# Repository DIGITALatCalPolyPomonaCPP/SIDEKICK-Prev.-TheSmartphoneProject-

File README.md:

# SIDEKICK — The Smartphone Project

**SIDEKICK, previously named TheSmartphoneProject, is DIGITAL @ Cal Poly Pomona's flagship systems-engineering project: a student-designed modular smartphone built around an FPGA-based computing platform.** It treats the phone as one integrated product spanning programmable logic, circuit design, embedded software, operating systems, sensing, user interaction, mechanical design, and thermal engineering.

<p align="center">
  
</p>

<p align="center"><em>FPGA smartphone mainboard prototype. <a href="https://photos.app.goo.gl/fKSVxjnxUvrLaF7E6">View the project photo album.</a></em></p>

**Repository status:** This is an archival engineering snapshot. It consolidates original design files, subsystem iterations, planning documents, curricula, and project updates that were previously distributed across multiple repositories and contributor archives. It does not claim that every subsystem reached production readiness or that the files currently assemble into a finished phone.

## Executive summary

Technology has always evolved. What has changed is the pace at which innovation reshapes the world around us. Entire industries can now emerge, mature, and reinvent themselves within the span of a student's undergraduate education. Artificial intelligence is reshaping knowledge-based work, robotics is moving from laboratories into homes and industry, and manufacturing is becoming increasingly autonomous.

**The technologies that will define our students' careers have not all been invented yet.**

Industry has responded by becoming increasingly interdisciplinary. The products that define modern society are rarely conceived, developed, or delivered through engineering alone. They emerge from engineering, business, operations, manufacturing, research, and design working toward a common objective.

DIGITAL @ Cal Poly Pomona was created in response to this shift. It does not replace traditional engineering education or the student organizations that apply it through competitions, research, and hands-on work. DIGITAL bridges the space between them by organizing around the process through which ideas become projects. Members investigate unfamiliar problems, research existing solutions, define requirements, evaluate trade-offs, establish scope, build prototypes, test assumptions, document decisions, and communicate across disciplines.

Few products demonstrate the importance of this process more clearly than the smartphone. Its significance comes not simply from replacing the telephone, but from integrating computing, communications, embedded systems, software, industrial design, manufacturing, supply-chain logistics, product management, and business strategy at global scale. SIDEKICK turns that integration challenge into an educational platform: students can specialize in one subsystem while learning how their decisions affect the complete product.

The projects will change. The technologies will change. What remains constant is the framework through which students learn to transform ideas into reality. Ultimately, the true product of DIGITAL is not the prototype; it is the people who leave the organization prepared to help define what comes next.

## Project definition

The project aims to engineer a working, custom-built mobile-device prototype whose central processing and hardware-control functions are implemented with field-programmable logic. Inspired by modern mobile architecture and open-source hardware, the team uses tools including KiCad, SolidWorks, ANSYS, AMD Vivado, and OrCAD to expose parts of the system that are normally hidden inside closed silicon and proprietary product stacks.

The intended phone should be comfortable to hold, intuitive to navigate, responsive under real use, and efficient enough for sustained daily operation. Success is therefore broader than a booting circuit board: the project pairs user evaluation of ergonomics, navigation, and responsiveness with engineering measurements such as clock speed, bus bandwidth, screen-on time, battery discharge, component efficiency, data integrity, latency, and thermal behavior.

As an educational platform, the phone gives students a way to follow a complete system from physical circuits and programmable logic through hardware interfaces, drivers, the operating system, and the user experience. The objective is not only a device, but a reusable foundation for learning, experimentation, repairability, and later product iterations.

## Planned operational architecture

The system concept separates the FPGA motherboard from modular peripheral hardware. Custom logic moves device data through controller and buffering stages into an AXI-based system fabric, where software drivers expose it to the operating system and user interface.

```mermaid
flowchart LR
    A[Peripheral daughterboard<br/>sensors and actuators] --> B[Custom SPI and GPIO logic]
    B --> C[Hardware FIFO buffers]
    C --> D[AXI interconnect and<br/>memory-mapped registers]
    E[FPGA processing core<br/>and programmable logic] --> B
    E --> D
    D --> F[OS kernel and drivers]
    F --> G[Touch UI, telemetry,<br/>audio and haptic feedback]
```

Representative system flows include:

- **Boot and biometric unlock:** power-rail bring-up, FPGA bitstream loading, kernel and driver initialization, fingerprint transfer, authentication, haptic confirmation, and UI unlock.
- **Continuous sensor telemetry:** IMU, temperature, ambient-light, and microphone sampling; serial-to-parallel conversion; cross-clock FIFO buffering; AXI transfer; and UI updates.

The current systems plan treats a peripheral-to-memory latency below 15 ms, lossless sensor-packet handling at the target sampling load, and passive heat routing away from user touchpoints as design requirements. These are project targets documented in the planning workspace, not certifications of the archived hardware.

## Development approach

The project follows a systems-engineering cycle:

1. define the product, user experience, and measurable requirements;
2. decompose the phone into coordinated electrical, computing, software, mechanical, and thermal workstreams;
3. select components and tools, establish interfaces, and procure hardware;
4. design and prototype subsystems independently;
5. integrate through defined buses, connectors, drivers, and mechanical boundaries;
6. test electrical, performance, power, thermal, usability, and integration risks; and
7. evaluate readiness, document results, and carry lessons into the next iteration.

The public [TheSmartphoneProject workspace](https://successful-twill-84f.notion.site/TheSmartphoneProject-3e3169473d7780c18205ee25701566bf) contains the living planning record, including the product definition, requirements, work breakdown, use-case material, sequence diagrams, activity diagrams, team plans, and subsystem task tracking. Some linked workspace records may have separate access controls.

## System overview

| Subsystem | Scope | Contents |
| --- | --- | --- |
| [FPGA main board and peripheral board](subsystems/fpga-mainboard/) | Central Zynq/FPGA architecture, power, RF/transceiver, USB, connectors, display peripheral board | KiCad source, fabrication outputs, 3D renders, manufacturing notes |
| [Haptics](subsystems/haptics/) | Tactile-feedback motor-driver board | KiCad project archive |
| [Fingerprint sensor](subsystems/fingerprint-sensor/) | Fingerprint-sensor interface board | KiCad project archive |
| [Flashlight](subsystems/flashlight/) | LM3644-based flashlight/LED driver | KiCad revisions and symbol/footprint library |
| [Mechanical and thermal](subsystems/mechanical-thermal/) | Phone enclosure, frame, assembly, and thermal/mechanical exploration | STEP, STL, SolidWorks, PDF, and archived CAD models |
| [Ambient-light sensor](subsystems/ambient-light-sensor/) | VCNL4030X01-based sensing board and additional light-sensor iterations | KiCad project archives and STEP model |
| [IMU](subsystems/imu/) | ICM-20948 inertial-sensing board and supporting power/level shifting | Seven chronological KiCad project archives |
| [Real-time clock](subsystems/real-time-clock/) | RV-3028-C8-based RTC board | KiCad source, component library, renders, schematics, and prototype outputs |
| [STM32 controller](subsystems/stm32-controller/) | STM32G431-based control and support electronics | KiCad design, component models/libraries, and STM32CubeIDE firmware project |
| [Heat sensor](subsystems/heat-sensor/) | Temperature/heat-sensing circuit exploration | KiCad schematic project archive |

## Project documentation

The [`documentation/`](documentation/) directory preserves the project record alongside the subsystem engineering files. It includes Hatchery proposals and phase updates, DIGITAL curriculum and mini-project decks, the project budget and bill-of-materials workbook, and organizational records. These originals are grouped by purpose and accompanied by checksums and provenance notes.

## Repository organization

Each subsystem has:

- a short README explaining what is present;
- a `PROVENANCE.md` with the original repository, branch, imported commit, and contributors; and
- a `source/` directory containing an unchanged snapshot of the files tracked at that commit.

The snapshots intentionally retain original filenames, archive structure, and intermediate revisions. This avoids silently selecting a “final” design where the source repository did not designate one.

## Opening the design files

Most electronics work is stored as KiCad projects, either directly or inside ZIP archives. Mechanical work includes STEP, STL, SolidWorks (`.SLDPRT`), and PDF files. Some archives contain KiCad automatic backups in addition to the latest project files.

Treat all outputs as historical engineering artifacts. Review schematics, footprints, stackups, component availability, electrical rules, and manufacturing requirements before fabrication.

## Project history and attribution

The initial source material was maintained across seven repositories under individual contributors and the DIGITAL organization. Additional project archives supplied directly by the project maintainer are recorded separately, without inferring authorship or repository history. See [CONTRIBUTORS.md](CONTRIBUTORS.md) for the contributor index and each subsystem's `PROVENANCE.md` for source details.

No authorship is transferred by this consolidation. Original Git history remains available through the linked source repositories and the immutable commit identifiers recorded here.

## Licensing

Licensing is **per subsystem**, not repository-wide. The FPGA/main-board snapshot includes its original GNU GPL v3 license. No explicit license file was present in the other source repositories at the recorded commits. See [LICENSES.md](LICENSES.md) before reusing or redistributing any material.

## About DIGITAL @ Cal Poly Pomona

DIGITAL is intentionally broader than one device, competition, technology, or discipline. Each initiative follows a shared project lifecycle: assess purpose and feasibility; define scope, requirements, risks, roles, and resources; execute and integrate through clear interfaces; document decisions continuously; and conclude with reflection, knowledge transfer, and a deliberate decision about what follows.

Systems engineering is the organization's foundation. It connects the complete product architecture with the technical and operational teams needed to deliver it, while allowing members to develop depth in hardware, software, mechanical design, thermal engineering, product design, business, or operations. SIDEKICK is DIGITAL's flagship reference implementation—not its fixed endpoint—and provides a concrete system through which this model can be tested and improved.

DIGITAL measures success beyond commercial readiness. Clear design decisions, robust interfaces, useful documentation, transferable skills, and member growth are outcomes in their own right. Read the archived [DIGITAL project proposal for Maximizing Engineering Potential](documentation/organization/DIGITAL_CPP_Project_Proposal_MEP.docx) for the organization's mission, values, project lifecycle, and structure.

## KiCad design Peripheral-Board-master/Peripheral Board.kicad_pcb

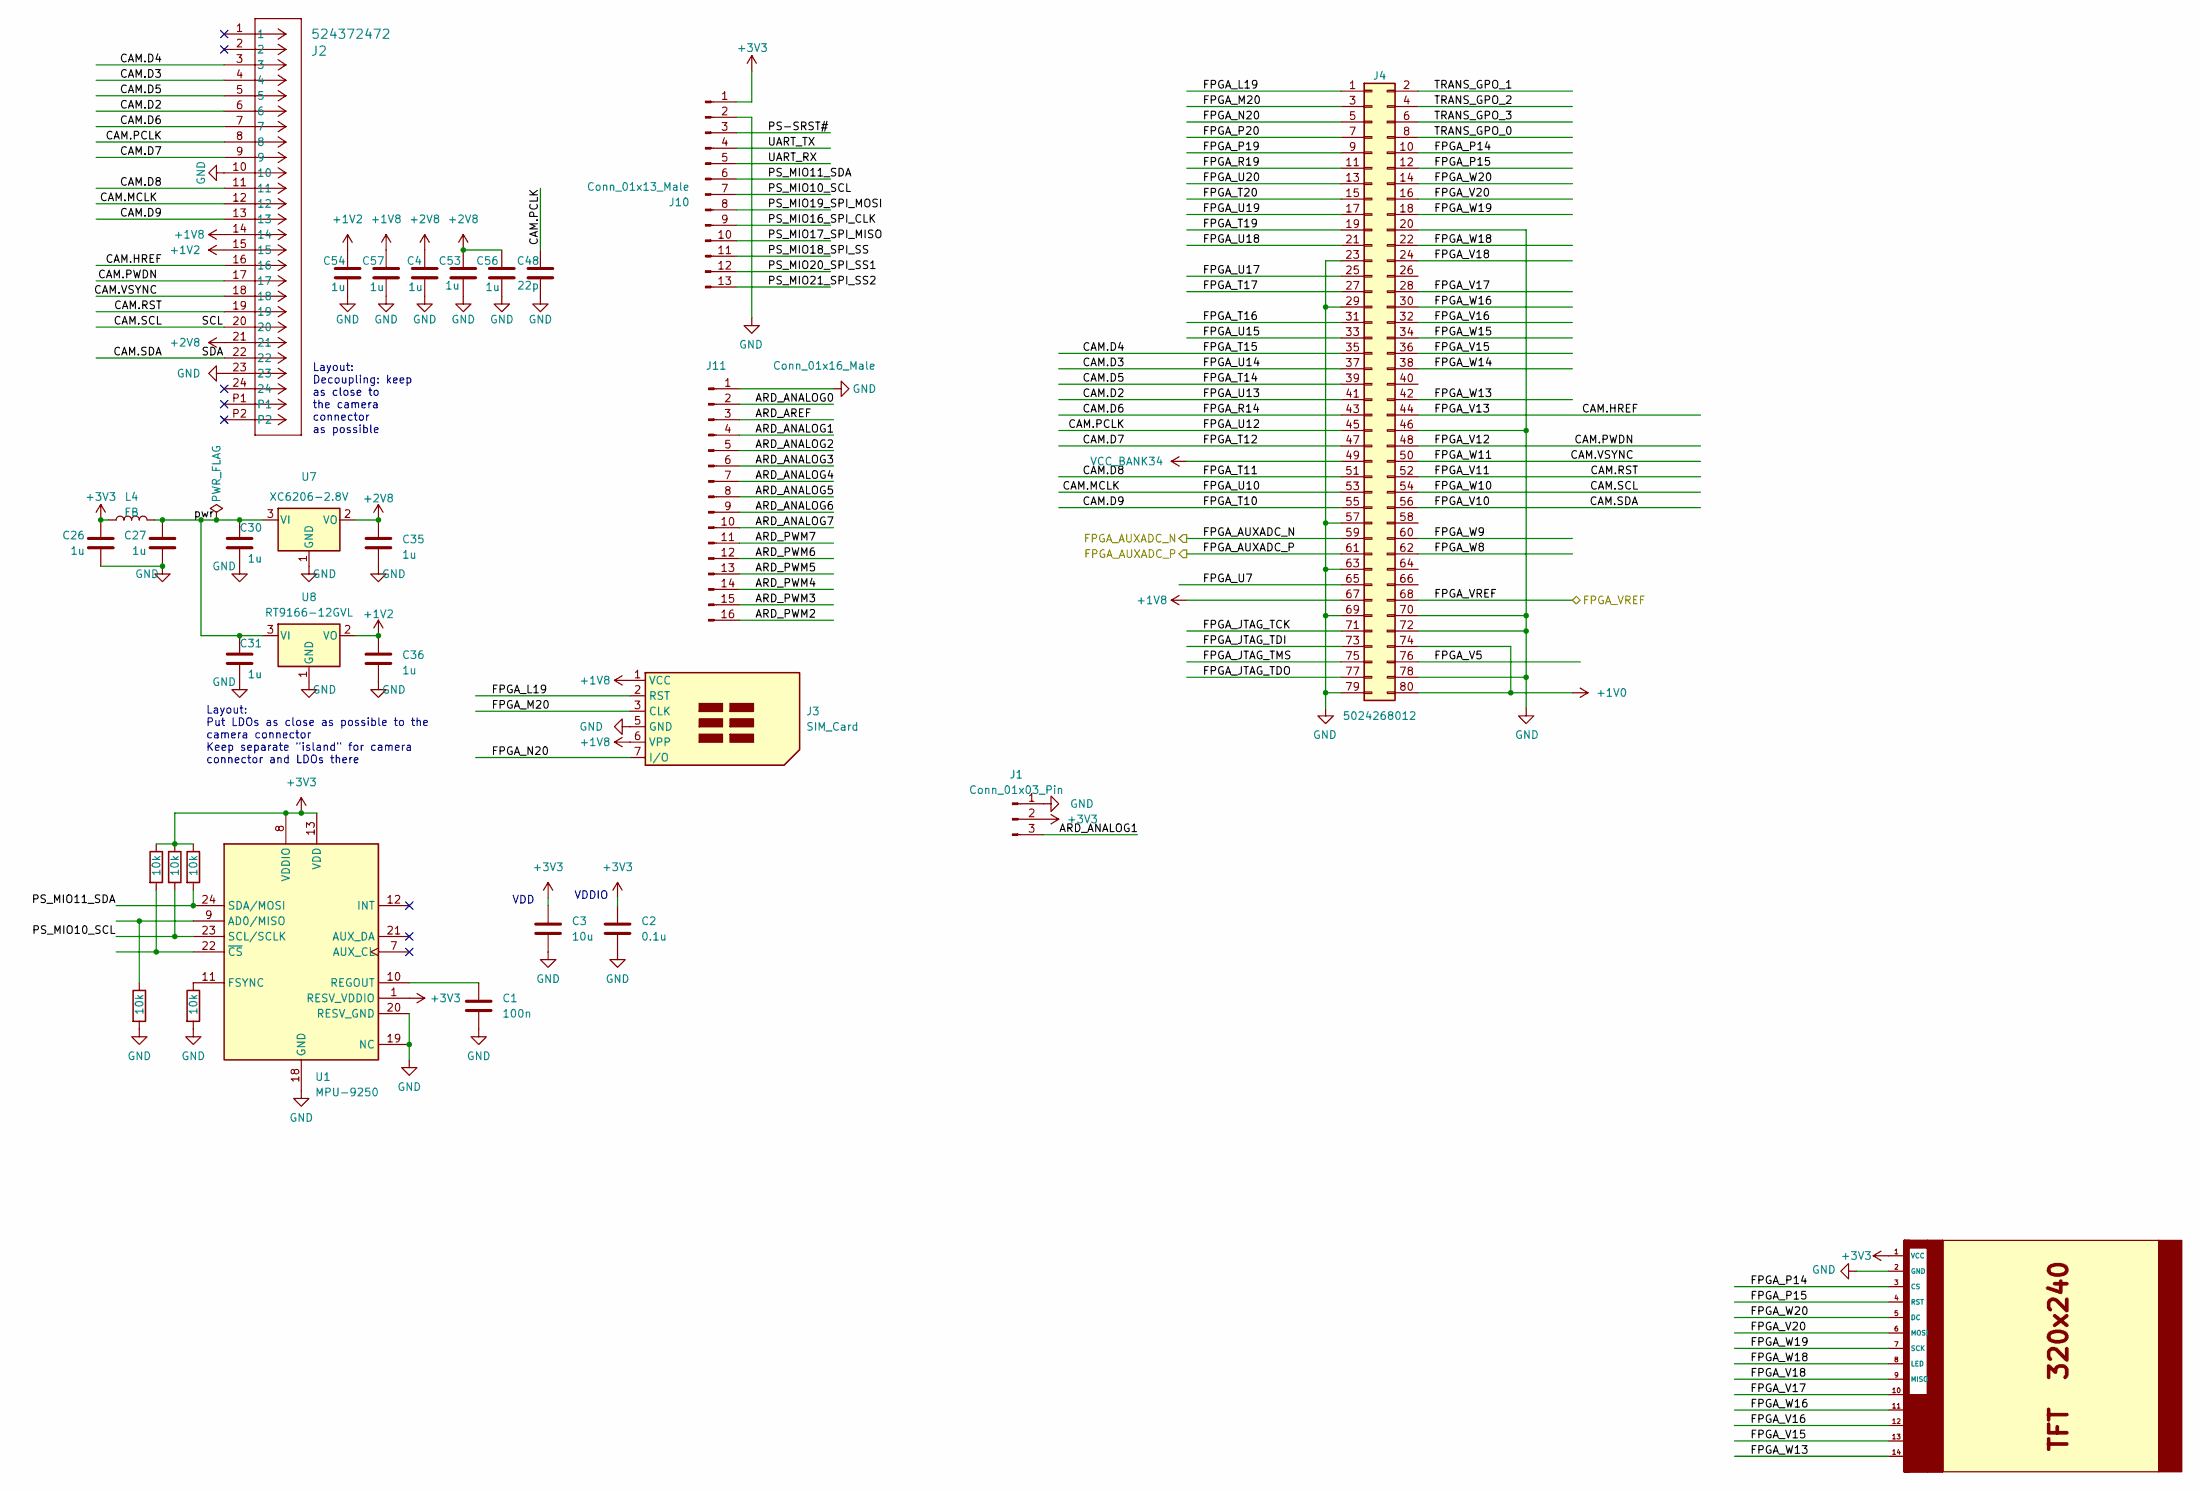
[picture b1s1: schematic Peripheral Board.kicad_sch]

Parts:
C1: 100n; C_0402_1005Metric_Pad0.74x0.62mm_HandSolder; LCSC C77020
C2, C3, C26, C27, C30, C31, C35, C36, C53: 10u_0402_CL05A105KA5NQNC; C_0402_1005Metric; Rating 25V; Tolerance 10%; MPN CL05A105KA5NQNC
C4, C54, C56, C57: 10u_0402_CL05A105KA5NQNC; C_0402_1005Metric; Tolerance 10%; Rating 25V; MPN CL05A105KA5NQNC
C48: 22p_0402_0402CG220J500NT; C_0402_1005Metric; Rating 50V; Tolerance 5%; MPN 0402CG220J500NT
J1: Conn_01x03_Pin; PinHeader_1x03_P2.54mm_Vertical
J2: 524372472; CON_524372472_MOL
J3: SIM_Card; nanoSIM_GCT_SIM8060-6-0-14-00
J4: 5024268012; Molex_SlimStack_502430-8010_2x40_P0.40mm_Vertical
J10: Conn_01x13_Male; PinHeader_1x13_P2.54mm_Vertical
J11: Conn_01x16_Male; PinHeader_1x16_P2.54mm_Vertical
L4: FB_2A_0805_220R@100MHz_BLM21PG221SN1D; L_0805_2012Metric_Pad1.15x1.40mm_HandSolder; Rating 2A; MPN BLM21PG221SN1D
R10, R11, R15, R16, R17: 10k; R_0402_1005Metric; LCSC C25543
U1: MPU-9250; InvenSense_QFN-24_3x3mm_P0.4mm
U5: TFT_320x240; TFT-320x240
U7: XC6206-2.8V; SOT-23; MPN XC6206-2.8V
U8: RT9166-12GVL; SOT-23; MPN RT9166-12GVL

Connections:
+1V0: J4.74, J4.80
+1V2: C36.1, C54.2, J2.15, U8.2 (VO)
+1V8: C57.2, J2.14, J3.1 (VCC), J3.6 (VPP), J4.67
+2V8: C4.2, C35.1, C53.1, C56.2, J2.21, U7.2 (VO)
+3V3: C2.1, C3.1, C26.1, J1.2, J10.1, L4.1, R10.1, R11.1, R15.1, U1.1 (RESV_VDDIO), U1.8 (VDDIO), U1.13 (VDD), U5.1 (VCC)
/ARD_ANALOG0: J11.2
/ARD_ANALOG1: J1.3, J11.4
/ARD_ANALOG2: J11.5
/ARD_ANALOG3: J11.6
/ARD_ANALOG4: J11.7
/ARD_ANALOG5: J11.8
/ARD_ANALOG6: J11.9
/ARD_ANALOG7: J11.10
/ARD_AREF: J11.3
/ARD_PWM2: J11.16
/ARD_PWM3: J11.15
/ARD_PWM4: J11.14
/ARD_PWM5: J11.13
/ARD_PWM6: J11.12
/ARD_PWM7: J11.11
/CAM.D2: J2.6, J4.41
/CAM.D3: J2.4, J4.37
/CAM.D4: J2.3, J4.35
/CAM.D5: J2.5, J4.39
/CAM.D6: J2.7, J4.43
/CAM.D7: J2.9, J4.47
/CAM.D8: J2.11, J4.51
/CAM.D9: J2.13, J4.55
/CAM.HREF: J2.16, J4.44
/CAM.MCLK: J2.12, J4.53
/CAM.PCLK: C48.1, J2.8, J4.45
/CAM.PWDN: J2.17, J4.48
/CAM.RST: J2.19, J4.52
/CAM.SCL: J2.20, J4.54
/CAM.SDA: J2.22, J4.56
/CAM.VSYNC: J2.18, J4.50
/FPGA_AUXADC_N: J4.59
/FPGA_AUXADC_P: J4.61
/FPGA_JTAG_TCK: J4.71
/FPGA_JTAG_TDI: J4.73
/FPGA_JTAG_TDO: J4.77
/FPGA_JTAG_TMS: J4.75
/FPGA_L19: J3.2 (RST), J4.1
/FPGA_M20: J3.3 (CLK), J4.3
/FPGA_N20: J3.7 (I/O), J4.5
/FPGA_P14: J4.10, U5.3 (CS)
/FPGA_P15: J4.12, U5.4 (RST)
/FPGA_P19: J4.9
/FPGA_P20: J4.7
/FPGA_R19: J4.11
/FPGA_T16: J4.31
/FPGA_T17: J4.27
/FPGA_T19: J4.19
/FPGA_T20: J4.15
/FPGA_U7: J4.65
/FPGA_U15: J4.33
/FPGA_U17: J4.25
/FPGA_U18: J4.21
/FPGA_U19: J4.17
/FPGA_U20: J4.13
/FPGA_V5: J4.76
/FPGA_V15: J4.36, U5.13
/FPGA_V16: J4.32, U5.12
/FPGA_V17: J4.28, U5.10
/FPGA_V18: J4.24, U5.9 (MISO)
/FPGA_V20: J4.16, U5.6 (MOSI)
/FPGA_VREF: J4.68
/FPGA_W8: J4.62
/FPGA_W9: J4.60
/FPGA_W13: J4.42, U5.14
/FPGA_W14: J4.38
/FPGA_W15: J4.34
/FPGA_W16: J4.30, U5.11
/FPGA_W18: J4.22, U5.8 (LED)
/FPGA_W19: J4.18, U5.7 (SCK)
/FPGA_W20: J4.14, U5.5 (DC)
/PS-SRST#: J10.3
/PS_MIO10_SCL: J10.7, R11.2, U1.23 (SCL/SCLK)
/PS_MIO11_SDA: J10.6, R10.2, U1.24 (SDA/MOSI)
/PS_MIO16_SPI_CLK: J10.9
/PS_MIO17_SPI_MISO: J10.10
/PS_MIO18_SPI_SS: J10.11
/PS_MIO19_SPI_MOSI: J10.8
/PS_MIO20_SPI_SS1: J10.12
/PS_MIO21_SPI_SS2: J10.13
/TRANS_GPO_0: J4.8
/TRANS_GPO_1: J4.2
/TRANS_GPO_2: J4.4
/TRANS_GPO_3: J4.6
/UART_RX: J10.5
/UART_TX: J10.4
/pwr: C27.1, C30.1, C31.1, L4.2, U7.3 (VI), U8.3 (VI)
GND: C1.2, C2.2, C3.2, C4.1, C26.2, C27.2, C30.2, C31.2, C35.2, C36.2, C48.2, C53.2, C54.1, C56.1, C57.1, J1.1, J2.10, J2.23, J3.5 (GND), J4.20, J4.23, J4.29, J4.46, J4.57, J4.63, J4.69, J4.70, J4.72, J4.78, J4.79, J10.2, J11.1, R16.2, R17.2, U1.18 (GND), U1.19 (NC), U1.20 (RESV_GND), U5.2 (GND), U7.1 (GND), U8.1 (GND)
unnamed: R17.1, U1.9 (AD0/MISO)
unnamed: R16.1, U1.11 (FSYNC)
unnamed: C1.1, U1.10 (REGOUT)
unnamed: R15.2, U1.22 (~CS)
VCC_BANK34: J4.49

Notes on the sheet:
VDD
Layout: Decoupling: keep as close to the camera connector as possible
Layout: Put LDOs as close as possible to the camera connector Keep separate "island" for camera connector and LDOs there
VDDIO

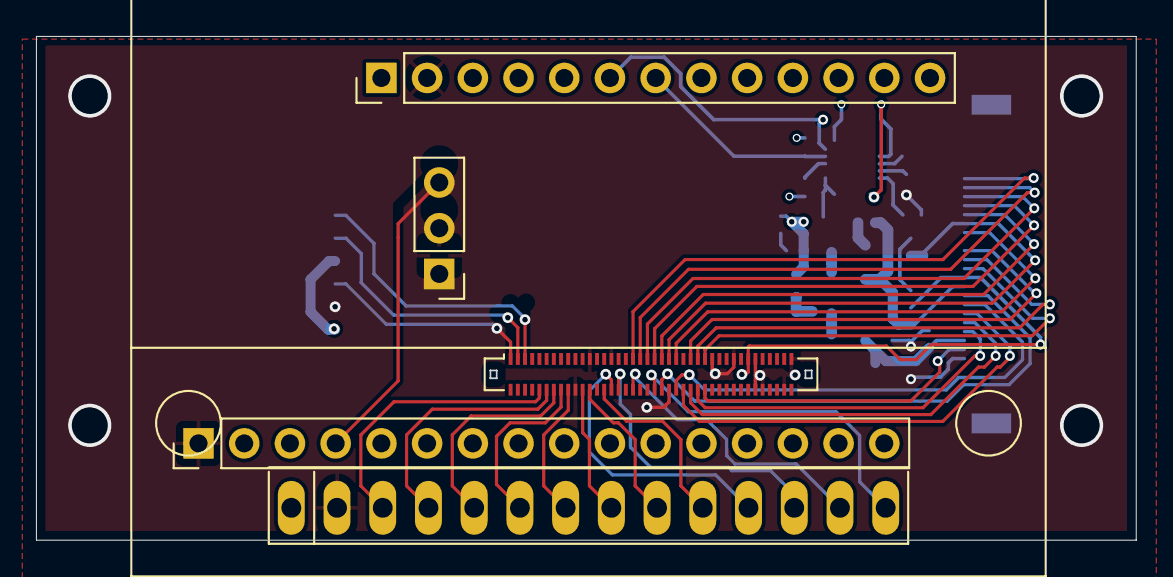
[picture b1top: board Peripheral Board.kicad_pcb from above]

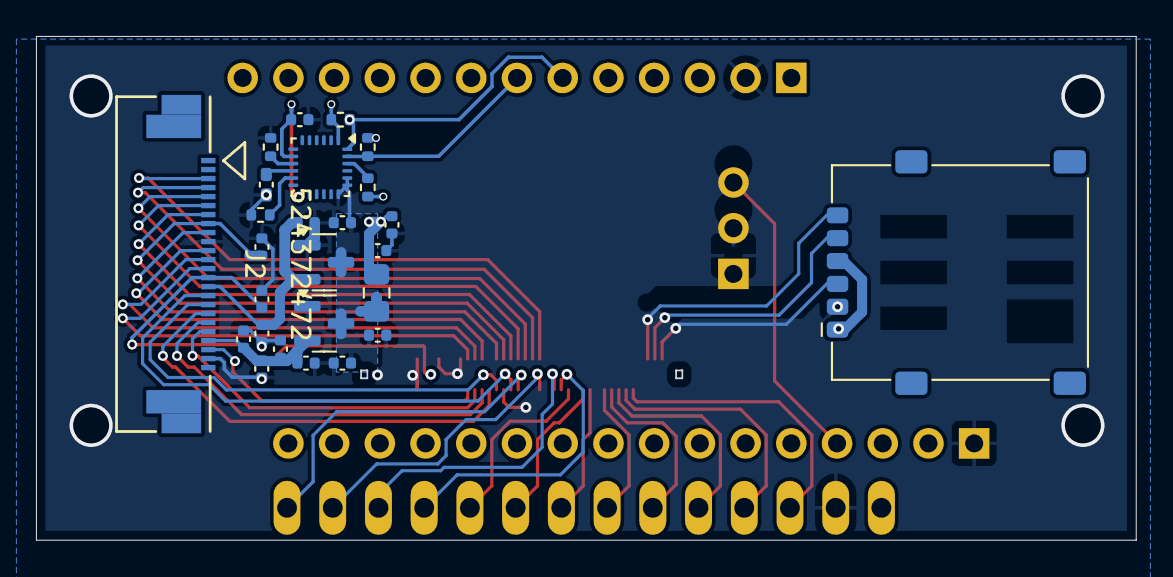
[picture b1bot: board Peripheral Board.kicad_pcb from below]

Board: 4 copper layers, 61.1 x 28.0 mm, 31 parts (26 on the bottom side), 45 nets.
